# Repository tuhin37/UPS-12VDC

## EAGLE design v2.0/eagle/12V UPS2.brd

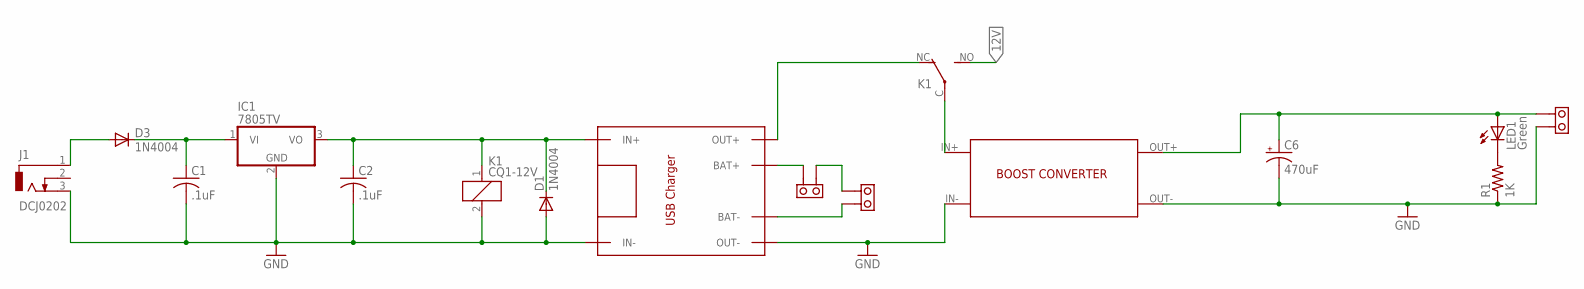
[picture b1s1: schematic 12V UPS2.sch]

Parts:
C1, C2: .1uF; C025-030X050
C6: 470uF; E5-8,5
D1, D3: 1N4004; DO41-10
IC1: 7805TV; TO220V
J1: DCJ0202
K1: CQ1-12V; CQ1
LED1: Green; LED5MM
R1: 1K; 0204V
U$1: TP4056_TH
U$2: BOOST
U$3, U$5, U$6: BERG_2

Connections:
12V: C1.1, D3.C, IC1.1 (VI), K1.NO (S)
BAT+: U$5.F, U$6.F
BAT-: U$1.BAT-, U$5.E
BOOST_IN+: K1.C, U$2.IN+
GND: C1.2, C2.2, C6.-, D1.A, IC1.2 (GND), J1.3, K1.2, R1.1, U$1.IN-, U$1.OUT-, U$2.IN-, U$2.OUT-, U$3.E
unnamed: D3.A, J1.1
unnamed: LED1.K (C), R1.2
unnamed: C2.1, D1.C, IC1.3 (VO), K1.1, U$1.IN+
unnamed: K1.NC (O), U$1.OUT+
unnamed: C6.+, LED1.A, U$2.OUT+, U$3.F
unnamed: U$1.BAT+, U$6.E

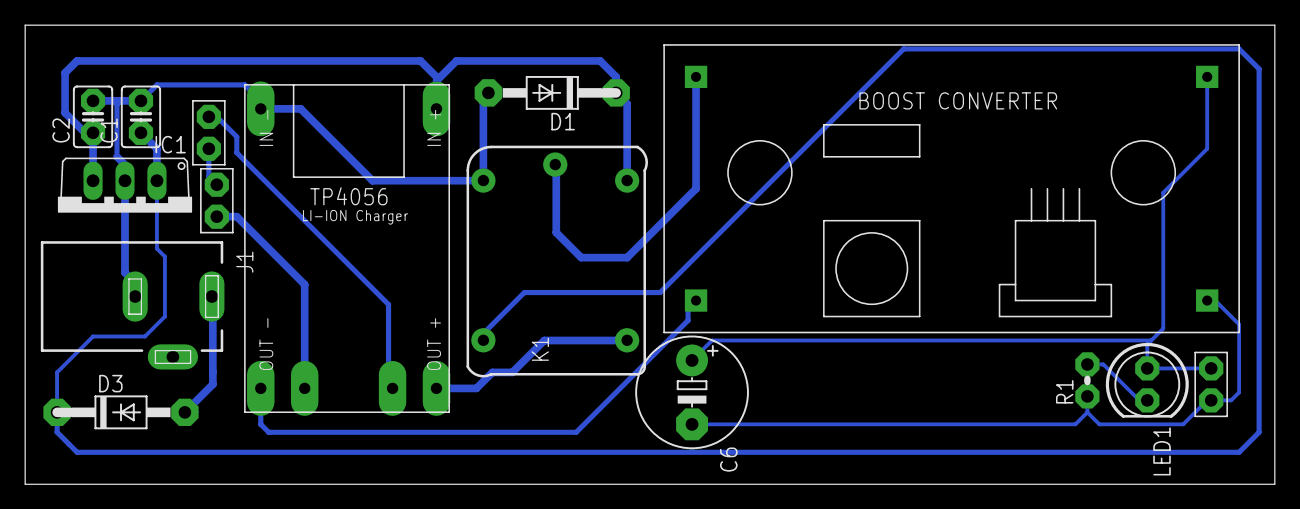
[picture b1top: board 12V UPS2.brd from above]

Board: 2 copper layers, 99.4 x 36.5 mm, 15 parts (0 on the bottom side), 11 nets.

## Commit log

2017-11-10 .gitignore created online with Bitbucket
2017-11-10 Add: Initial Files
2017-11-10 Add: Documentation in V2.0
2017-11-10 Edit: Creator name
